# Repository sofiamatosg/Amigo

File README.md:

# Amigo
Repository for Solder YSWS, from HackClub. I made a keychain shaped like a cute chick, my friend's favorite animal.
# Schematic

# PCB

# Features
* LEDs that light up when it's dark
* Vibration motor activated by pushbutton, so you can let stress go away!
* Cool silkscreen in the front and back
* Adorable chick shape
# BOM
* 3 LEDs
* 1 vibration motor
* 1 battery cell CR2032
* 3 resistors 220Ω
* 1 resistor 4.7kΩ
* 1 photoresistor GL5528
* 1 transistor 2N3904
> Slack username: Sofia G.
> 
> Slack ID: U07V87SQ9NK

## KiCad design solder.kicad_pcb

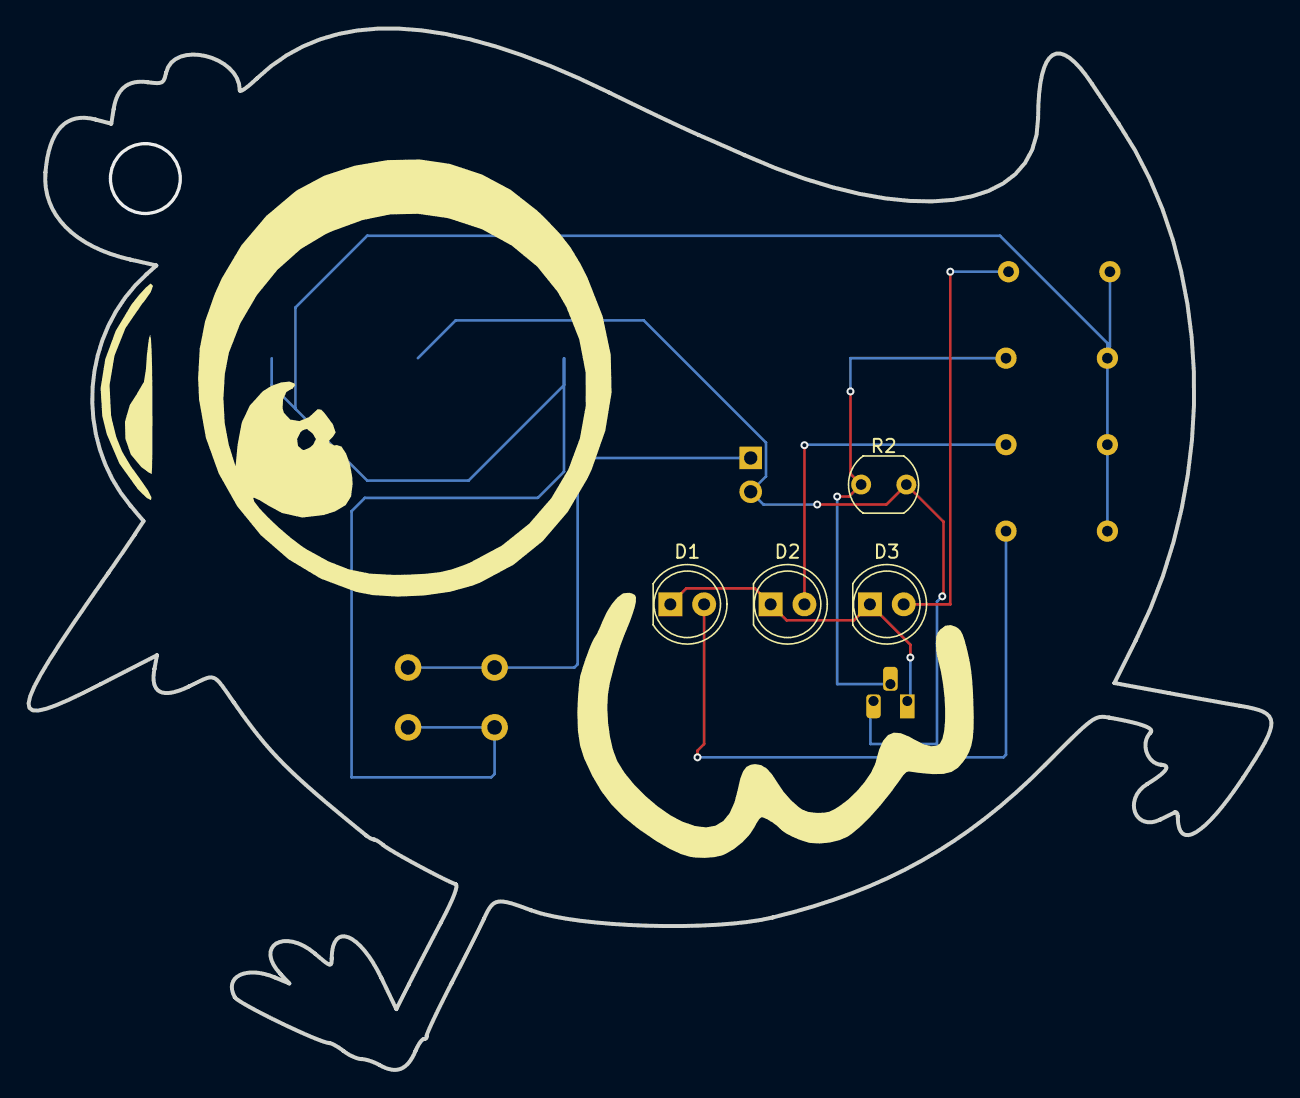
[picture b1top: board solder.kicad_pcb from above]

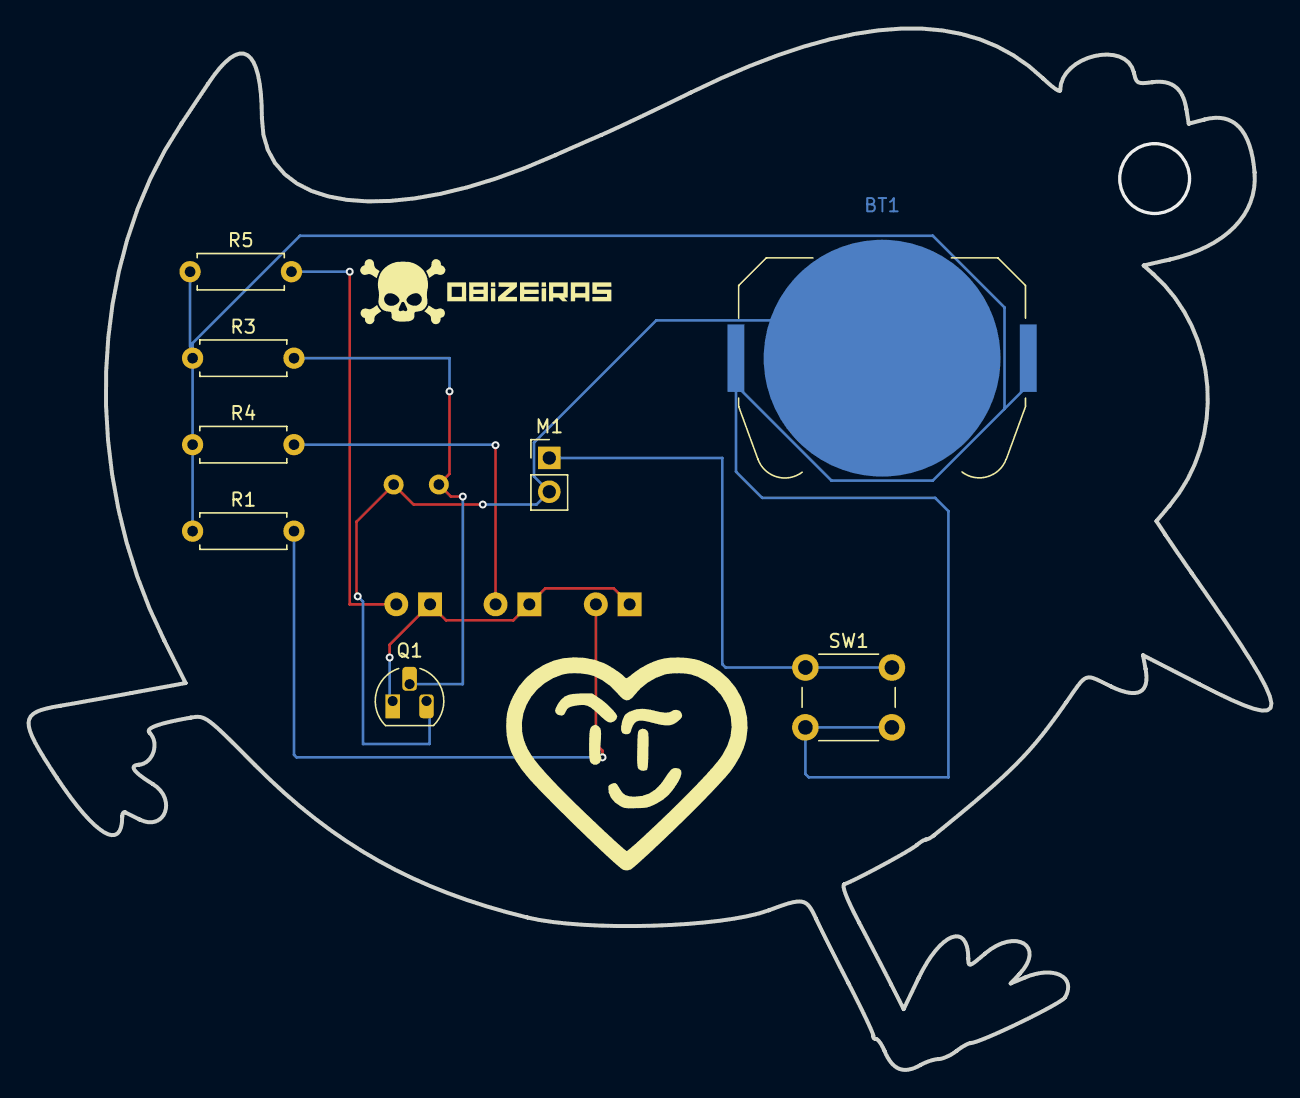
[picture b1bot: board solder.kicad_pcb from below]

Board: 2 copper layers, 93.4 x 78.3 mm, 12 parts (8 on the bottom side), 8 nets.

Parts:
BT1: Battery_Cell; BatteryHolder_Keystone_3034_1x20mm
D1, D2, D3: LED; LED_D5.0mm
M1: Motor_DC; PinHeader_1x02_P2.54mm_Vertical
Q1: NPN; TO-92L_HandSolder
R1, R3, R4, R5: R; R_Axial_DIN0207_L6.3mm_D2.5mm_P7.62mm_Horizontal
R2: R_Photo; R_LDR_5.1x4.3mm_P3.4mm_Vertical
SW1: SW_Push; SW_PUSH_6mm

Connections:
unnamed: BT1.1 (+), R1.1, R3.1, R4.1, R5.1, SW1.2
unnamed: BT1.2 (-), M1.2 (-), Q1.3 (E), R2.2
unnamed: D1.2 (A), R1.2
unnamed: D1.1 (K), D2.1 (K), D3.1 (K), Q1.1 (C)
unnamed: D2.2 (A), R4.2
unnamed: D3.2 (A), R5.2
unnamed: M1.1 (+), SW1.1
unnamed: Q1.2 (B), R2.1, R3.2

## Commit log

2025-06-30 Final README.md
2025-06-30 Typo README.md
